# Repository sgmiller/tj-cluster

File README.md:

# tj-cluster
A custom PCB and software to drive Jeep TJ/XJ Dash clusters' CCD bus and receive CAN messages.

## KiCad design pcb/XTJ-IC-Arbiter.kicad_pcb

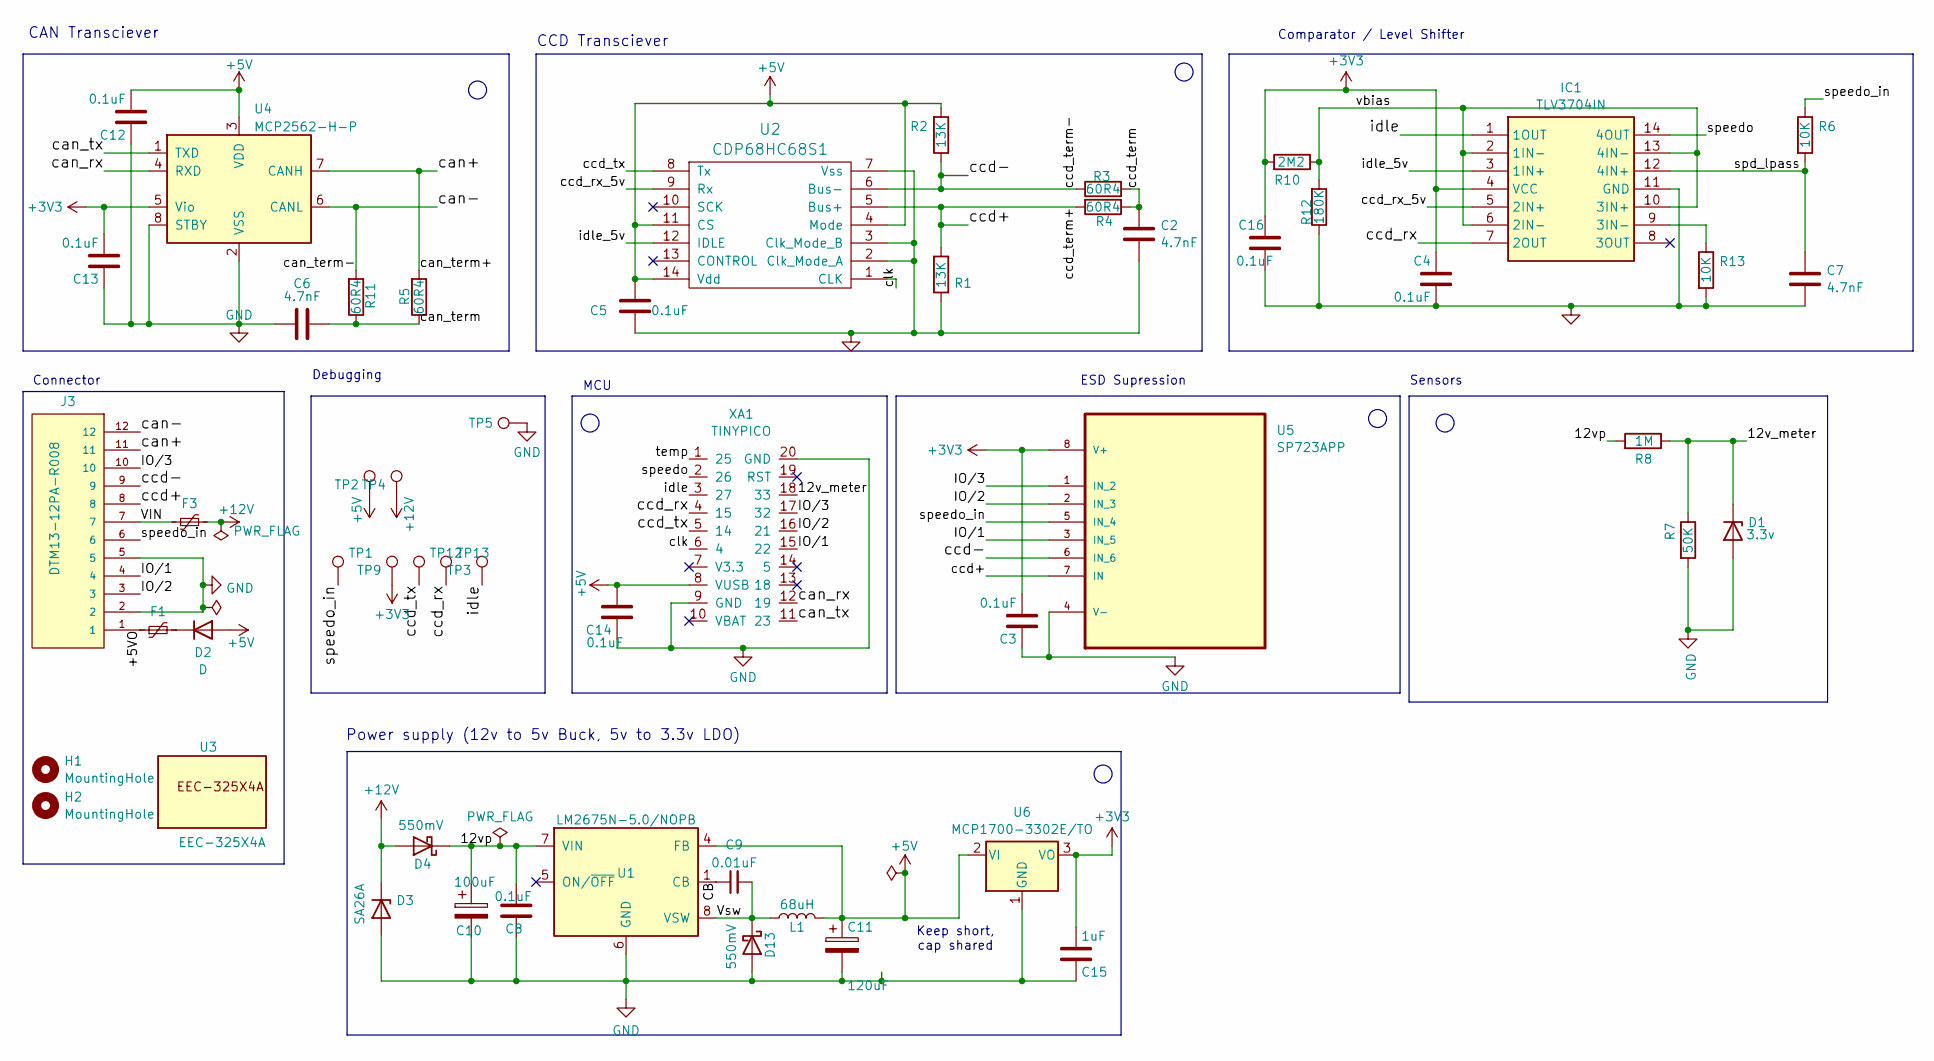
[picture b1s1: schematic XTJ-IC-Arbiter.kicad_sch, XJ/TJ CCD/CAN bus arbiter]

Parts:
C2, C6, C7: 4.7nF; C_Disc_D3.8mm_W2.6mm_P2.50mm; MPN AR151C472K4R
C3, C4, C5, C8, C12, C13, C14, C16: 0.1uF; C_Disc_D4.7mm_W2.5mm_P5.00mm; MPN K103K10X7RF53L2
C9: 0.01uF; C_Disc_D3.8mm_W2.6mm_P2.50mm; MPN K103K10X7RF53L2
C10: 100uF; C_Radial_D8.0mm_H11.5mm_P3.50mm; MPN EEU-FR1V101
C11: 120uF; CP_Radial_D8.0mm_P3.50mm; MPN EEU-FR1H121L
C15: 1uF; FA24; MPN FA24X7R1H105KRU06
D1: 3.3v; D_DO-35_SOD27_P7.62mm_Horizontal; MPN TZX3V3B-TR
D2: D; D_DO-41_SOD81_P7.62mm_Horizontal; MPN 1N40001GH
D3: SA26A; D_DO-15_P10.16mm_Horizontal; MPN SA26A; Mouser Part Number 576-SA26CA
D4, D13: 550mV; D_DO-41_SOD81_P7.62mm_Horizontal; MPN MBR160RLG
F1, F3: Polyfuse_Small; Fuse_1812_4532Metric_Pad1.30x3.40mm_HandSolder; MPN MF-MSMF050/30X-2
H1, H2: MountingHole; MountingHole_3mm
IC1: TLV3704IN; DIP794W53P254L1930H508Q14N; Mouser Part Number 595-TLV3704IN
J3: DTM13-12PA-R008; TE_DTM13-12PA-R008
L1: 68uH; L_Radial_D7.8mm_P5.00mm_Fastron_07HCP; MPN 744731680
R1, R2: 13K; R_Axial_DIN0207_L6.3mm_D2.5mm_P7.62mm_Horizontal; MPN MF1/4DC1302F
R3, R4, R5, R11: 60R4; R_Axial_DIN0207_L6.3mm_D2.5mm_P7.62mm_Horizontal; MPN CMF5560R400FHEK
R6, R13: 10K; R_Axial_DIN0207_L6.3mm_D2.5mm_P7.62mm_Horizontal; MPN MF1/4DC4701F
R7: 50K; R_Axial_DIN0207_L6.3mm_D2.5mm_P7.62mm_Horizontal; MPN MF1/4DC4701F
R8: 1M; R_Axial_DIN0207_L6.3mm_D2.5mm_P7.62mm_Horizontal; MPN MFR-25FBF52-100K
R10: 2M2; R_Axial_DIN0207_L6.3mm_D2.5mm_P7.62mm_Horizontal; MPN MF1/4LCT52R225J
R12: 180K; R_Axial_DIN0207_L6.3mm_D2.5mm_P7.62mm_Horizontal; MPN MF1/4DCT52R1803F
TP1, TP3, TP5, TP12, TP13: TestPoint; TestPoint_Loop_D2.50mm_Drill1.0mm; MPN 534-5267
TP2, TP4, TP9: TestPoint; TestPoint_Plated_Hole_D2.0mm; MPN 534-5267
U1: LM2675N-5.0/NOPB; DIP-8_W7.62mm; MPN LM2675N-5.0/NOPB
U2: CDP68HC68S1; DIP-14_W7.62mm; MPN CDP68HC68S1
U3: EEC-325X4A; TE_EEC-325X4A; PARTREV F
U4: MCP2562-H-P; DIP-8_W7.62mm; MPN MCP2562-H-P
U5: SP723APP; DIP-8_W7.62mm; MPN SP723APP
U6: MCP1700-3302E/TO; TO-92_Inline_Wide; MPN MCP1700-3302E/TO
XA1: TINYPICO

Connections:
+3V3: C3.2, C4.1, C13.2, C15.2, C16.2, IC1.4 (VCC), R10.2, TP9.1, U4.5 (Vio), U5.8 (V+), U6.3 (VO)
+5V: C5.2, C11.1, C12.2, C14.2, D2.2 (A), L1.2, R2.2, TP2.1, U1.4 (FB), U2.4 (Mode), U2.11 (CS), U2.14 (Vdd), U4.3 (VDD), U6.2 (VI), XA1.8 (VUSB)
+12V: D3.1 (K), D4.2 (A), F3.2, TP4.1
/12v_meter: D1.1 (K), R7.1, R8.1, XA1.18 (33)
/12vp: C8.2, C10.1, D4.1 (K), R8.2, U1.7 (VIN)
/+5VO: F1.1, J3.1
/CB: C9.1, U1.1 (CB)
/IO/1: J3.4, U5.3 (IN_5), XA1.15 (22)
/IO/2: J3.3, U5.2 (IN_3), XA1.16 (21)
/IO/3: J3.10, U5.1 (IN_2), XA1.17 (32)
/VIN: F3.1, J3.7
/Vsw: C9.2, D13.1 (K), L1.1, U1.8 (VSW)
/can+: J3.11, R5.2, U4.7 (CANH)
/can-: J3.12, R11.2, U4.6 (CANL)
/can_rx: U4.4 (RXD), XA1.12 (19)
/can_term: C6.2, R5.1, R11.1
/can_tx: U4.1 (TXD), XA1.11 (23)
/ccd+: J3.8, R1.2, R4.2, U2.5 (Bus+), U5.7 (IN)
/ccd-: J3.9, R2.1, R3.1, U2.6 (Bus-), U5.6 (IN_6)
/ccd_rx: IC1.7 (2OUT), TP13.1, XA1.4 (15)
/ccd_rx_5v: IC1.5 (2IN+), U2.9 (Rx)
/ccd_term: C2.2, R3.2, R4.1
/ccd_tx: TP12.1, U2.8 (Tx), XA1.5 (14)
/clk: U2.1 (CLK), XA1.6 (4)
/idle: IC1.1 (1OUT), TP3.1, XA1.3 (27)
/idle_5v: IC1.3 (1IN+), U2.12 (IDLE)
/spd_lpass: C7.2, IC1.12 (4IN+), R6.2
/speedo: IC1.14 (4OUT), XA1.2 (26)
/speedo_in: J3.6, R6.1, TP1.1, U5.5 (IN_4)
/temp: XA1.1 (25)
/vbias: IC1.2 (1IN-), IC1.6 (2IN-), IC1.10 (3IN+), IC1.13 (4IN-), R10.1, R12.2
GND: C2.1, C3.1, C4.2, C5.1, C6.1, C7.1, C8.1, C10.2, C11.2, C12.1, C13.1, C14.1, C15.1, C16.1, D1.2 (A), D3.2 (A), D13.2 (A), IC1.11 (GND), J3.2, J3.5, R1.1, R7.2, R12.1, R13.2, TP5.1, U1.6 (GND), U2.2 (Clk_Mode_A), U2.3 (Clk_Mode_B), U2.7 (Vss), U4.2 (VSS), U4.8 (STBY), U5.4 (V-), U6.1 (GND), XA1.9 (GND), XA1.20 (GND)
unnamed: D2.1 (K), F1.2
unnamed: IC1.9 (3IN-), R13.1

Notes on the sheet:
CAN Transciever
MCU
Debugging
Sensors
CCD Transciever
ESD Supression
Power supply (12v to 5v Buck, 5v to 3.3v LDO)
Keep short, cap shared
Comparator / Level Shifter
Connector

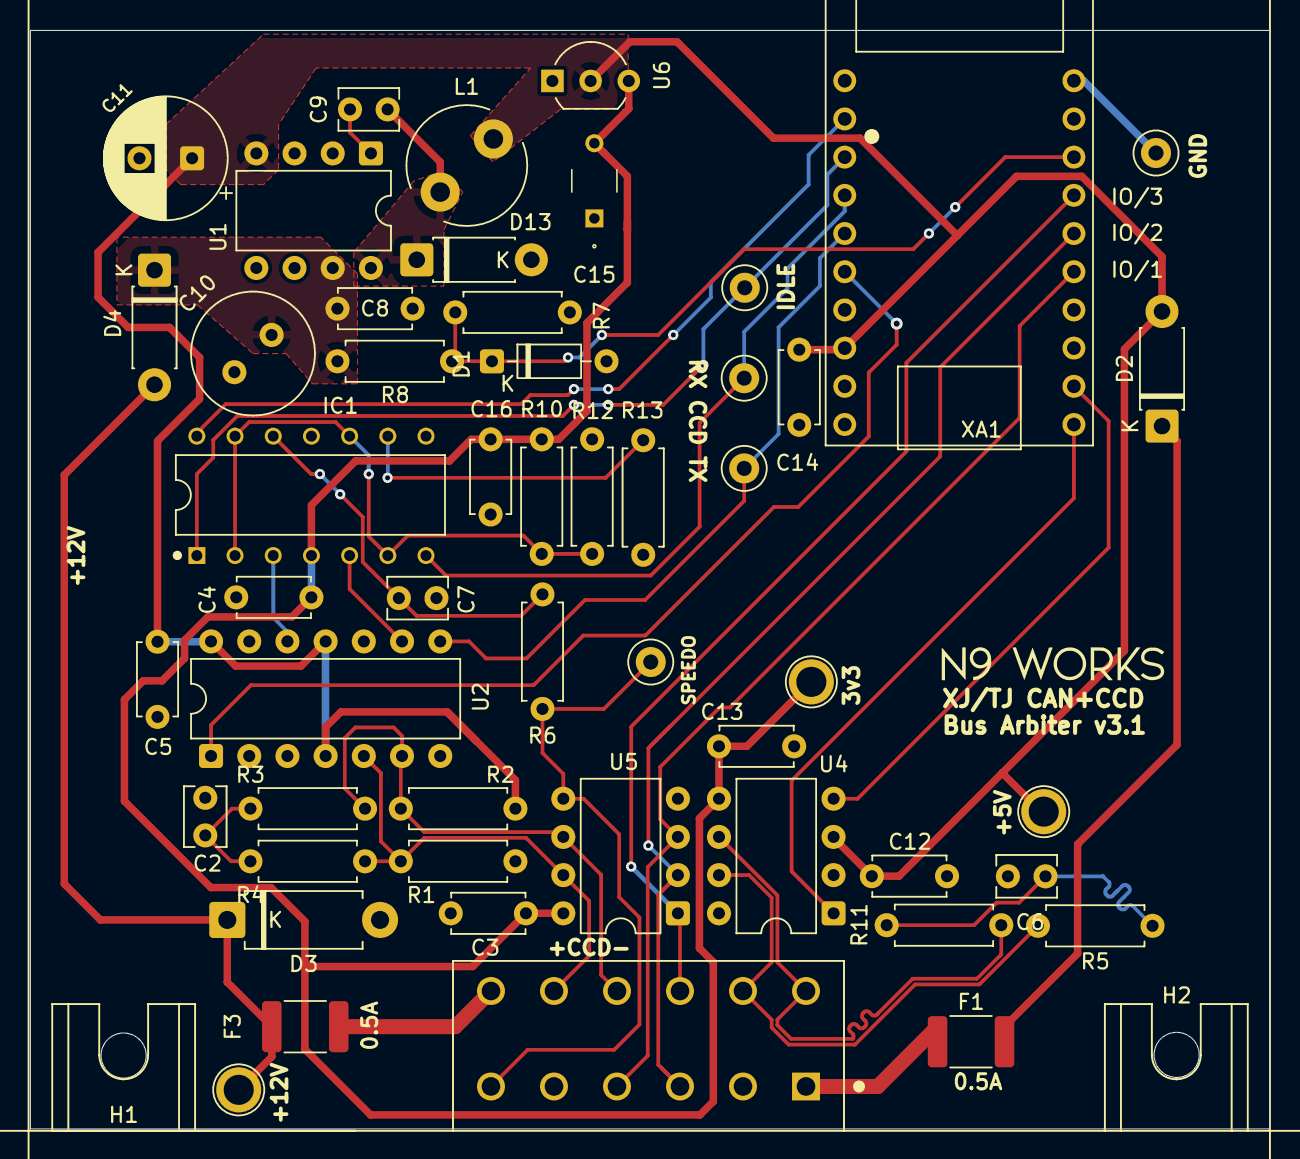
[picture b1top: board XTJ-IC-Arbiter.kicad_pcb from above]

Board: 2 copper layers, 82.4 x 73.0 mm, 54 parts (0 on the bottom side), 33 nets.

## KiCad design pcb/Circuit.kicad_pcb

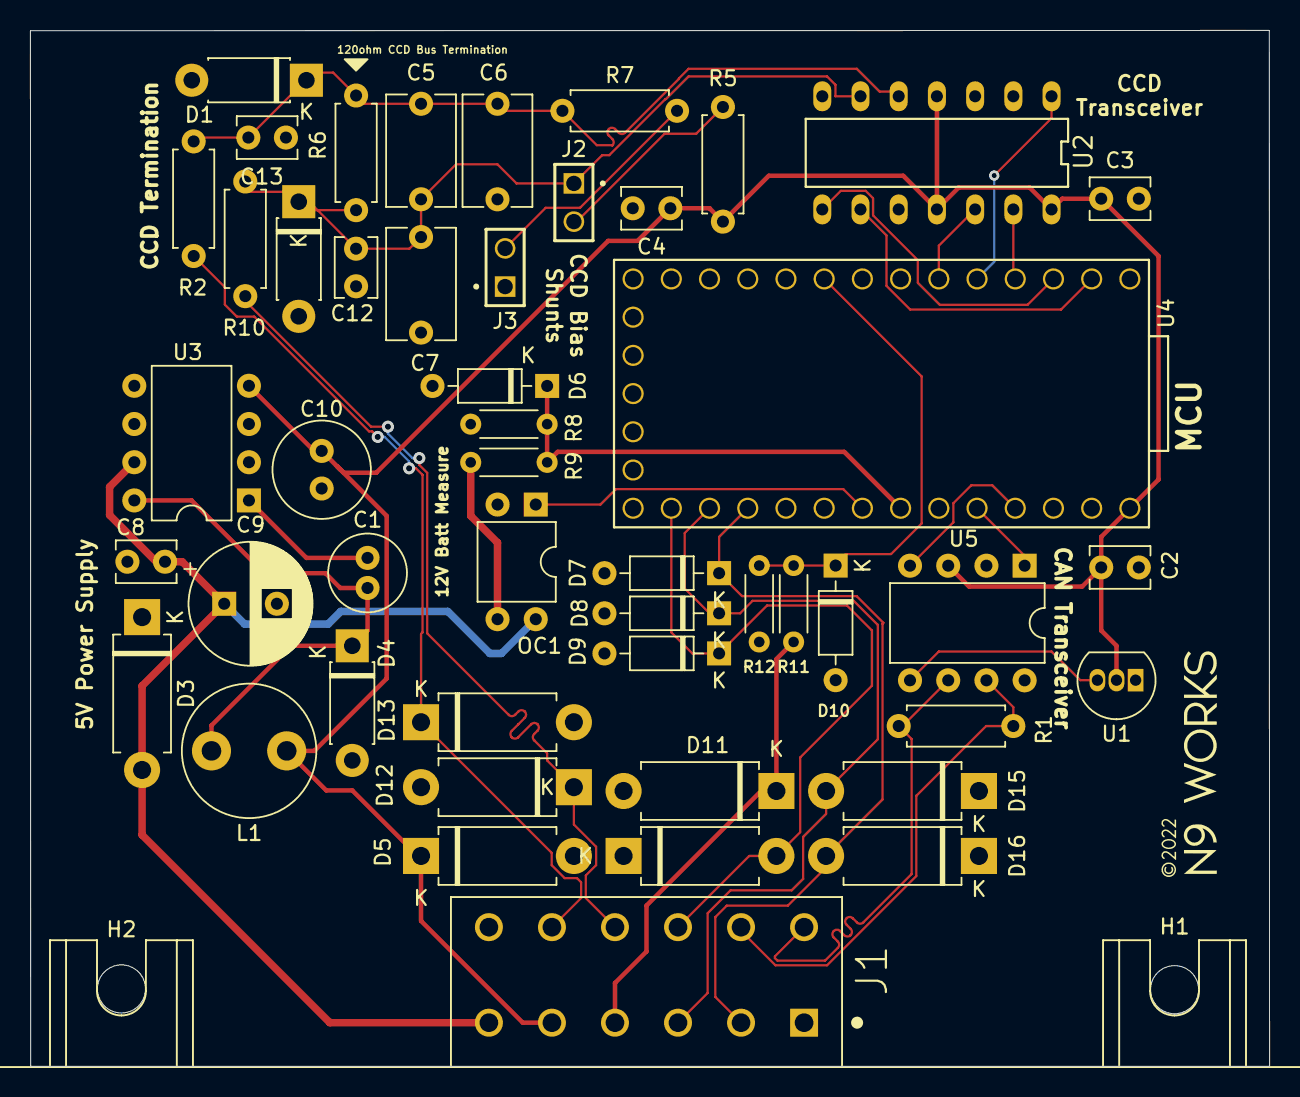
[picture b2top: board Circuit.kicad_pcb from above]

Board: 2 copper layers, 82.4 x 68.9 mm, 51 parts (0 on the bottom side), 29 nets.

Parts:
   : LOGO; N9Works
C1: 10nF; C_Radial_D5.0mm_H11.0mm_P2.00mm
C2, C3, C4: 0.1uF; C_Disc_D3.8mm_W2.6mm_P2.50mm
C5, C6, C7: 25pF; C_Disc_D6.5mm_W4mm_P6.4mm
C8: 0.1uf; C_Disc_D3.8mm_W2.6mm_P2.50mm
C9: 100uF; CP_Radial_D8.0mm_P3.50mm
C10: 68uF; C_Radial_D6.3mm_H7.0mm_P2.50mm
C12, C13: 3.3nF; C_Disc_D3.8mm_W2.6mm_P2.50mm
D1, D2: 1N4728; D_DO-41_SOD81_P7.62mm_Horizontal
D3: P6KE39CA; D_DO-15_P10.16mm_Horizontal
D4: 550mV; D_DO-41_SOD81_P7.62mm_Horizontal
D5, D14: P6KE6.8A; D_DO-15_P10.16mm_Horizontal
D6, D7, D8, D9, D10: 3.3v; D_DO-35_SOD27_P7.62mm_Horizontal
D11, D15, D16: P6KE6.8CA; D_DO-15_P10.16mm_Horizontal
D12, D13: SA5.0CA; D_DO-15_P10.16mm_Horizontal
H1, H2: MountingHole_Pad; MountingHole_3.2mm_M3
J1: DTM13-12PA-R008; TE_DTM13-12PA-R008
J2, J3: TSW-101-07-T-D; SAMTEC_TSW-101-07-T-D
L1: 47uH; L_Radial_D8.7mm_P5.00mm_Fastron_07HCP
OC1: Optocoupler_Generic; DIP-4_W7.62mm
R1, R6: 120ohm; R_Axial_DIN0207_L6.3mm_D2.5mm_P7.62mm_Horizontal
R2, R10: 10ohm; R_Axial_DIN0207_L6.3mm_D2.5mm_P7.62mm_Horizontal
R5, R7: 13K; R_Axial_DIN0207_L6.3mm_D2.5mm_P7.62mm_Horizontal
R8: 2.2Kohm; R_Axial_DIN0204_L3.6mm_D1.6mm_P5.08mm_Horizontal
R9: 13Kohm; R_Axial_DIN0204_L3.6mm_D1.6mm_P5.08mm_Horizontal
R11: 15K; R_Axial_DIN0204_L3.6mm_D1.6mm_P5.08mm_Horizontal
R12: 10K; R_Axial_DIN0204_L3.6mm_D1.6mm_P5.08mm_Horizontal
U1: MCP1700-1802E_TO92; TO-92_Inline
U2: CDP68HC68S1
U3: LM2672N-5.0; DIP-8_W7.62mm
U4: Teensy4.0; Teensy40_NoSMT
U5: MCP2562-H-P; DIP-8_W7.62mm

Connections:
12V_MEASCTL: OC1.1, U4.26 (19_A5_SCL0)
12V_MEASURE: D6.1 (K), R8.1, R9.1, U4.27 (20_A6_TX5_LRCLK1)
+5V: C2.1, C3.1, C4.1, C10.1, D5.1 (K), J1.5, L1.2, R5.1, U1.2 (VI), U2.4 (Mode), U2.11 (CS), U2.14 (Vdd), U3.4 (FB), U4.33 (VIN), U5.3 (VDD)
+12V: C8.1, C9.1, D3.2 (A), J1.6, OC1.4, U3.7 (VIN)
/1v8: U1.3 (VO), U5.5 (Vio)
CCD_CLOCK: U2.1 (CLK), U4.5 (3_LRCLK2)
GND: C2.2, C3.2, C4.2, C6.2, C7.2, C8.2, C9.2, C10.2, C12.2, C13.2, D1.2 (A), D2.2 (A), D3.1 (K), D4.2 (A), D5.2 (A), D6.2 (A), D7.2 (A), D8.2 (A), D9.2 (A), D10.2 (A), D11.1 (K), D12.2 (A), D13.2 (A), D14.2 (A), D15.1 (K), D16.1 (K), J1.1, J1.7, J3.01, OC1.2, R8.2, R12.1, U1.1 (GND), U2.2 (Clk_Mode_A), U2.3 (Clk_Mode_B), U2.7 (Vss), U3.6 (GND), U4.1 (GND), U4.17 (GND), U4.32 (GND), U5.2 (VSS), U5.8 (STBY)
IO/1: D7.1 (K), D16.2 (A), J1.2, U4.23 (16_A2_RX4_SCL1)
IO/2: D8.1 (K), D15.2 (A), J1.3, U4.22 (15_A1_RX3_SPDIF_IN)
IO/3: D9.1 (K), D11.2 (A), J1.10, U4.21 (14_A0_TX3_SPDIF_OUT)
unnamed: C1.1, U3.1 (CB)
unnamed: C1.2, D4.1 (K), L1.1, U3.8 (VSW)
unnamed: J2.02, R5.2
unnamed: J3.02, R7.2
unnamed: OC1.3, R9.2
SPEEDO: D10.1 (K), R11.1, R12.2, U4.9 (7_RX2_OUT1A)
SPEEDO_IN: D14.1 (K), J1.4, R11.2
can+: J1.11, R1.1, U5.7 (CANH)
can-: J1.12, R1.2, U5.6 (CANL)
can_rx: U4.30 (23_A9_CRX1_MCLK1), U5.4 (RXD)
can_tx: U4.29 (22_A8_CTX1), U5.1 (TXD)
ccd+: D13.1 (K), J1.8, R2.1
ccd-: D12.1 (K), J1.9, R10.1
ccd_f+: C5.1, C6.1, C13.1, D1.1 (K), R2.2, R6.1, R7.1, U2.5 (Bus+)
ccd_f-: C5.2, C7.1, C12.1, D2.1 (K), J2.01, R6.2, R10.2, U2.6 (Bus-)
ctrl: U2.13 (CONTROL), U4.4 (2_OUT2)
idle: U2.12 (IDLE), U4.6 (4_BCLK2)
rxd: U2.9 (Rx), U4.2 (0_RX1_CRX2_CS1)
txd: U2.8 (Tx), U4.3 (1_TX1_CTX2_MISO1)

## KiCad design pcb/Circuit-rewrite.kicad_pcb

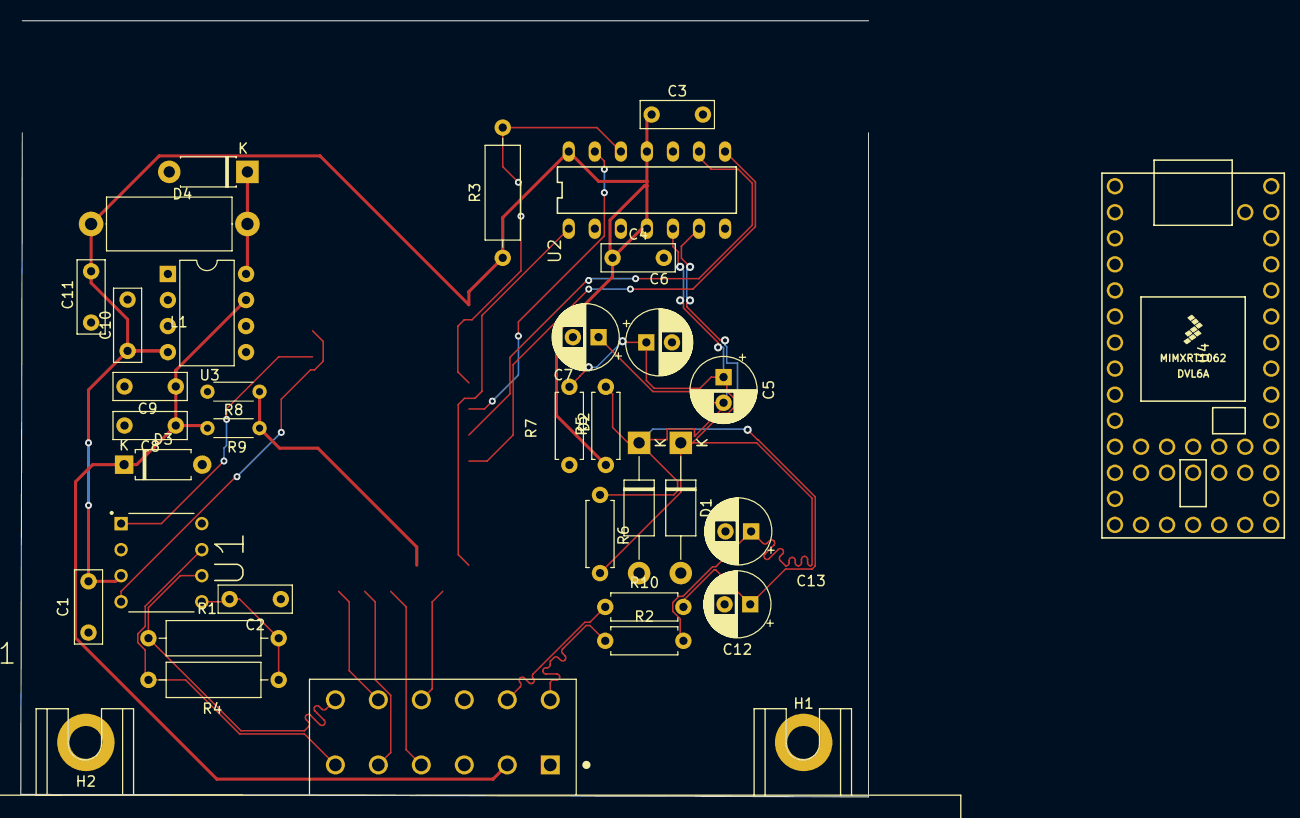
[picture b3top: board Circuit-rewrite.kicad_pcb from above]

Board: 2 copper layers, 82.7 x 75.7 mm, 35 parts (0 on the bottom side), 23 nets.

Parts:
C1, C3, C4: 0.1uF; C_Disc_D7.0mm_W2.5mm_P5.00mm
C2: 4700pF; C_Disc_D7.0mm_W2.5mm_P5.00mm
C5, C6, C7: 25pF; CP_Radial_D6.3mm_P2.50mm
C8, C11: 0.1uf; C_Disc_D7.0mm_W2.5mm_P5.00mm
C9: 100uf; C_Disc_D7.0mm_W2.5mm_P5.00mm
C10: 150uF; C_Disc_D7.0mm_W2.5mm_P5.00mm
C12, C13: 3.3nF; CP_Radial_D6.3mm_P2.50mm
D1, D2: 1N4728; D_DO-41_SOD81_P12.70mm_Horizontal
D3: SD15_SOD323; D_A-405_P7.62mm_Horizontal
D4: 550mV; D_DO-41_SOD81_P7.62mm_Horizontal
H1, H2: MountingHole_Pad; MountingHole_3.2mm_M3_DIN965_Pad
J1: DTM13-12PA-R008; TE_DTM13-12PA-R008
L1: 150uH; L_Axial_L12.0mm_D5.0mm_P15.24mm_Horizontal_Fastron_MISC
R1, R4: 60ohm; R_Axial_DIN0309_L9.0mm_D3.2mm_P12.70mm_Horizontal
R2, R10: 10ohm; R_Axial_DIN0207_L6.3mm_D2.5mm_P7.62mm_Horizontal
R3: 10k; R_Axial_DIN0309_L9.0mm_D3.2mm_P12.70mm_Horizontal
R5, R7: 13K; R_Axial_DIN0207_L6.3mm_D2.5mm_P7.62mm_Horizontal
R6: 120ohm; R_Axial_DIN0207_L6.3mm_D2.5mm_P7.62mm_Horizontal
R8: 1.5M; R_Axial_DIN0204_L3.6mm_D1.6mm_P5.08mm_Horizontal
R9: 10M; R_Axial_DIN0204_L3.6mm_D1.6mm_P5.08mm_Horizontal
U1: MCP2561; DIP787W46P254L927H533Q8
U2: CDP68HC68S1
U3: LM2594HVM-5.0; DIP-8_W7.62mm
U4: Teensy4.0; Teensy40

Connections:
12V_MEASURE: R8.1, R9.1, U4.38 (27_A13_SCK1)
+5V: C1.2, C3.1, C4.1, C10.1, C11.1, L1.2, R3.1, R5.1, U1.3 (VDD), U2.4 (Mode), U2.11 (CS), U2.14 (Vdd), U3.4 (FB), U4.33 (VIN)
+12V: C8.1, C9.1, D3.1 (A1), J1.2, R9.2, U3.7 (VIN)
/IO/1: J1.8, U4.43 (32_OUT1B)
/IO/2: J1.9, U4.35 (24_A10_TX6_SCL2)
/IO/3: J1.5, U4.41 (30_CRX3)
/IO/4: J1.4, U4.39 (28_RX7)
CCD_CLOCK: U2.1 (CLK), U4.23 (16_A2_RX4_SCL1)
GND: C1.1, C2.1, C3.2, C4.2, C6.2, C7.2, C8.2, C9.2, C10.2, C11.2, C12.2, C13.2, D1.2 (A), D2.2 (A), D3.2 (A2), D4.2 (A), H1.1, H2.1, J1.1, R7.2, R8.2, U1.2 (VSS), U2.2 (Clk_Mode_A), U2.3 (Clk_Mode_B), U2.7 (Vss), U3.1 (NC), U3.2 (NC), U3.3 (NC), U3.5 (~ON/OFF), U3.6 (GND), U4.1 (GND), U4.17 (GND), U4.32 (GND)
unnamed: C2.2, R1.2, R4.1, U1.5 (SPLIT)
unnamed: D4.1 (K), L1.1, U3.8 (OUT)
can+: J1.6, R1.1, U1.7 (CANH)
can-: J1.7, R4.2, U1.6 (CANL)
can_rx: U1.4 (RXD), U4.2 (0_RX1_CRX2_CS1)
can_tx: U1.1 (TXD), U4.3 (1_TX1_CTX2_MISO1)
ccd+: J1.12, R2.1
ccd-: J1.11, R10.1
ccd_f+: C5.1, C6.1, C13.1, D1.1 (K), R2.2, R6.1, R7.1, U2.5 (Bus+)
ccd_f-: C5.2, C7.1, C12.1, D2.1 (K), R5.2, R6.2, R10.2, U2.6 (Bus-)
ctrl: U2.13 (CONTROL), U4.29 (22_A8_CTX1)
idle: R3.2, U2.12 (IDLE), U4.30 (23_A9_CRX1_MCLK1)
rxd: U2.9 (Rx), U4.28 (21_A7_RX5_BCLK1)
txd: U2.8 (Tx), U4.27 (20_A6_TX5_LRCLK1)

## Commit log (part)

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2022-02-06 Initial PlatformIO setup
2022-05-31 Initial success
2022-06-02 begin abstraction
2022-06-03 Working speedometer
2022-06-05 Add PCB
2022-06-05 Add gitignore
2022-06-08 Working oil and battery gauges
2022-06-08 Not these
2022-06-08 Cleanup code, add all instruments
2022-06-08 speedometer
2022-06-08 make constant
2022-06-09 Implement Teensy watchdog, and light the SKIM lamp if we reset due to it
2022-06-09 Code for speedometer handling and odometer increment (not quite)
2022-06-09 More git ignore
2022-06-10 Blink onboard LED on activity
2022-06-10 Airbag handling
2022-06-10 more tweaks
2022-06-11 commit before changing can transceiver
2022-06-12 Save design with LEDs
2022-06-14 Move IO pins to more useful Teensy pins
2022-06-14 Add footprints
2022-06-14 linting
2022-06-14 remove gerbers
2022-06-14 more footprints
2022-06-14 Update teensy footprint
2022-06-14 Remove unnecessary files
2022-06-15 Start self test mode
2022-06-15 Found upshift and cruise, added to selftest
2022-06-15 get rid of ancient rewrite
2022-06-16 Move speedo to a FlexPWM pin
2022-06-24 Update for actual parts ordered from Mouser
2022-06-27 Circuit using LM2591HVT
2022-06-28 CDP 3d model
2022-06-28 Tidy up capacitors
2022-06-28 move via cleanup
2022-06-29 Add overvoltage protection to the 12v measure pin
2022-06-29 Implement odometer increment
2022-06-30 Add 3.3v overvolt protection zeners
2022-06-30 Use correctly sized TVS diodes for the CCD bus
2022-06-30 Move CCD lines farther from power
2022-06-30 Silkscreen tweaks
2022-07-01 Undo attempt to simplify jumpers
2022-07-01 Project rename
2022-07-01 Complete rename
2022-07-01 Refactor away the need for interval timers, which we have in limited quantity
2022-07-05 Multi-CCD experiment
2022-07-05 fix activity
2022-07-05 Add voltage divider for idle
2022-07-05 rearrange
2022-07-08 series resistor for idle in
2022-07-08 ignore fab
2022-07-08 More small tweaks
2022-07-08 Copy changes from the multi-ccd branch
2022-07-08 Rationalize CCD filters
2022-07-09 Re-add TVS diodes to CCD inputs
2022-07-09 Geographical reannotate
2022-07-09 Experiment with a TVS IC
2022-07-10 Slightly reorganize TVS matrix to clean up traces
2022-07-10 gitignore
2022-07-17 remove mounting grounds
2022-07-17 Shorten distance to bypass capacitor
2022-07-17 After breadboarding, eliminate LDO reference regulator
2022-07-17 Correct DRC errors
2022-07-17 Add parallel traces to CAN/CCD routes so there is still a connection if the 120ohm resistor is cut
2022-07-18 More tweaking
2022-07-18 Switch from jumpers to DIP switches for CCD bias, CCD bus termination. Add DIP switch for selectable CAN bus termination. DIP switches should hold up in vibration, where I worry a jumper might rattle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
2022-07-18 Some hypothetical CAN handling for the AEM VCU
2022-07-19 Add a level shifter to handle 5v to 3.3v for the CDP<->Teensy
2022-07-19 tidy wiring
2022-07-21 Tidy up even more vias
2022-07-21 Improve a couple grounds
2022-07-24 Concept ignoring all CCD RX
2022-07-24 cleanup
2022-07-24 diff tuning
2022-07-26 Switch to a MOSFET array
2022-07-27 Switch to simpler THT transistors
2022-07-27 Rewire
2022-07-27 tweak
2022-07-27 Try to change to 3.3v
2022-07-27 Design using the CDP transceiver but in TX only, neglecting idle etc
2022-07-27 Add repeated refresh of all instruments
2022-07-28 Rearrange for tighter CCD signal traces
2022-07-28 CCD length tuning
2022-07-28 Fully working self test!
2022-07-28 Tweak CCD routing just a bit more
2022-07-29 Measure battery more frequently
2022-07-29 Straightforward airbag interval handling
2022-07-29 Eureka! Finally satisfied with CCD traces
2022-07-29 One more bypass cap
2022-07-30 Last minute tweaks and board shrink
2022-07-31 Footprint double-checks
2022-07-31 Correct and arrange power components
2022-07-31 Don't crowd the ground
2022-07-31 Fix battery calculation
2022-07-31 Fix auto-refresh logic
2022-07-31 CCD length tune
2022-07-31 Last tweaks before manufacture
2022-07-31 Correct one of the ESD diodes
2022-08-01 Add a readme for the source code
2022-08-01 formatting
2022-08-01 speedo note
2022-09-10 Fixes for CCD filter network
2022-09-10 and schematic
2022-09-10 Re-length tune
2022-09-10 Accidental commit
2022-09-11 Add a couple backup traces
2022-09-12 Correct orientation of CCD chip, which was electrically sound but the 3D model was backwards
2022-09-17 More mods for 1.1
2022-10-16 Don't place 5v and 12v pins side by side
2022-10-16 Add overvoltage protection on the 5v line
2022-10-16 move k
2022-10-18 Add a test header
2024-05-24 Fixes prior to simplification
2024-05-24 not a success
2024-05-25 Get rid of errors
2024-05-25 Finished!
2024-05-25 exclusions
2024-05-26 tune can termination length
2024-05-26 fix board edge
2024-05-26 cleanup bypass caps
2024-05-26 get rid of 5v feed text
2024-05-26 convert unused pin to gnd
2024-05-26 fix 3d model offset for connectr
2024-05-26 3.3v conn
2024-05-26 safer 3.3v trace
2024-05-26 drc fixes
2024-05-26 fix orphaned c9
2024-05-26 fix unconnected pullup
2024-05-26 one more bypass
2024-05-26 resolve
2024-05-26 Switch to single pole dip switches for CCD/CAN termination
2024-05-27 warnings
2024-05-27 elminate some vias
2024-05-27 current limiting on the ssd, tune can length
2024-05-27 Fix TVS diode for 12v to have reasonable working/breakdown ranges
2024-05-28 current limit the 12v measure prior to the ssd
2024-05-28 cleanup schematic
2024-05-28 get input capacitor closer to power ic
2024-05-28 Tune CAN lengths
2024-05-28 labels
2024-05-28 logo & copyright
2024-05-28 bypass cap for tvs array
2024-05-29 tune ccd bus length
2024-05-30 death to vias
2024-06-01 Recalculate the 12v measure voltage dividers, and add a zener to limit to 3.3v
2024-06-01 ugly but functional
2024-06-01 less ugly
2024-06-01 polish, text
2024-06-01 oshpark colors
2024-06-04 no battery relay
2024-06-06 bigger courtyard for the ccd module
2025-08-30 Update to KiCad 9
2025-08-31 Fix labels
2025-09-02 Working v3 layout
2025-09-02 other parts
2025-09-02 Silkscreen cleanup
2025-09-02 more updates
2025-09-02 update pins
2025-09-02 differential skew tuning
2025-09-04 drive towards 0 errors
2025-09-04 ignore KiCad locks
2025-09-04 Software pin updates, label test points on PCB
2025-09-04 Correct the power supply Cout specs
2025-09-06 Power 3.3v via a separate LDO rather than from the Teensy
2025-09-07 Add tons of detail and fixes to particular part numbers and footprints
2025-09-07 part data
2025-09-08 Swich to jumpers for bus termination
2025-09-08 Cleanup labels
2025-09-08 Fix buffer footprint
2025-09-08 Teensy 3D model
2025-09-08 change tx/rx pins
2025-09-08 ERC fixes
2025-09-09 Ditch test points for vertical passives
2025-09-09 More layout tweaks, mostly around power
2025-09-10 Version using a TinyPICO ESP32 board
2025-09-10 fix CAN SPLIT termination
2025-09-12 Get BOM part #s correct
2025-09-12 further work on specifying components
2025-09-13 schematic cleanup
2025-09-13 Switch from label to proper power symbol for 3.3v
2025-09-15 Add a transistor to boost a weak speedo signal
2025-09-16 Add input cap for LDO
2025-09-17 update for parts I can actually purchase
2025-09-17 Avoid routing under the antenna
2025-09-17 even more
2025-09-17 remove probably bad idea diode
2025-09-18 Continued routing improvements
2025-09-18 vscode settings
2025-09-20 Add the correct TE footprint including courtyard. Update antenna keep-out, more finesse
2025-09-20 Fix gnd plane
2025-09-20 Fix last minute inconsistencies
2025-09-20 among other things, creating more USB connector clearance
2025-09-20 length tune the extended I/Os, making it at least possible to use them for high speed signals
2025-09-20 Keep voltage test points at board edge to avoid shorts
2025-09-20 fix DRC errors
2025-09-20 silkscreen fixes
2025-09-23 Re-layout power supply based on TI guidance and getting to know copper pours
2025-09-23 tidy up schematic
2025-09-23 add enclosure symbol/footprint
2025-09-23 still working to keep a clean ground plane
2025-09-24 try and fix the position of the enclosure keepout
2025-09-24 Lock board, enclosure, edge cuts, and connector
2025-09-24 F.Cu ground pour
2025-09-26 Continued pour zone optimization
2025-09-27 Keep power traces 0.05in from board edge, via rule
2025-09-27 Via stitching
2025-09-27 tie unused GPIOs to GND
2025-09-27 dont actually connect pins to ground, as that could result in a short if the pin is configured as output
2025-09-27 Get 12v measure closer to source
2025-09-29 uniform power net, shielding via stitching
2025-09-29 ensure ext I/Os are length tuned
2025-10-01 Speedo needs an internal pullup
2025-10-01 After the 4 layer adventure, cleanup
2025-10-03 Hand tune the differential lengths (CAD/CCD)
2025-10-03 silkscreen work
2025-10-04 re-route some traces to get contiguous front ground pours without vias
2025-10-06 LDO caps were the wrong footprint
2025-10-07 Other footprint fixes
2025-10-07 colorize crucial nets
2025-10-07 fusing
2025-10-08 12v inrush limiting
2025-10-08 use a slow blow fuse to avoid a heat producing inrush resistor
2025-10-11 Add comparator
2025-10-12 Layout tweaks
2025-10-12 resolve erc/drc errors
2025-10-12 net clarification
2025-10-13 tidy
2025-10-15 Add an ambient thermometer, and use it to sleep the ESP32 if we get too hot. Presumably it'll be the MCU that gets us there
2025-10-15 move it to a cleaner spot
2025-10-15 aesthetics
2025-10-17 relayout the board to get the antenna out to the edge with no copper beneath
2025-10-18 work on eliminating b.cu routes
2025-10-18 Fix CDP clock signal
2025-10-18 Lots of the signals coming out of the CDP are >0v at low, provide a ref volt for V- to the comparator for those
2025-10-18 respond to erc violations
2025-10-18 USB connector keepout
2025-10-18 stiching vias
2025-10-19 make the comparator's VREF configurable in the MCU
2025-10-19 Turns out the ESP32 DAC isn't very clean on analog, so use a voltage divider/RC for the comparator reference
2025-10-20 fix rule violations
2025-10-20 Double check and tune board edges
2025-10-22 Wrong TVS diode for 12v, need only be uni-dir
2025-10-22 dev env files
2025-10-23 reduce ground via tracks
2025-10-23 missed swapping the tvs diode bypass cap when rotating
2025-10-28 Some more routing opt, fix up ref labels
2025-10-30 Wider base track widths, stitching vias
2025-10-31 improve clearance
2025-10-31 eliminate f.cu pour
2025-10-31 dont overthink tinypico thermals
2025-10-31 via elimination
2025-10-31 re-tune CCD traces
2025-11-01 more iteration
2025-11-02 better isolation of power traces and power pins in the connector
2025-11-06 Working Bluetooth serial
2025-11-06 .gitignore
2025-11-07 Switch to 1a fast blow fuses.
2025-11-07 use conditional code for self-test vs normal etc
2025-11-08 re-layout switcher for lower emi
2025-11-08 Lots of fun cleanup made possible by the supply re-layout
2025-11-08 silkscreen
2025-11-10 battery wip
2025-11-10 change bat vdiv values
2025-11-12 Add an input side diode to the regulator circuit to prevent reverse voltage when USB is connected but 12v is not
2025-11-12 schottky on output too
2025-11-14 work on math for speedo
2025-11-15 teardrop power nets
2025-11-15 fix comparator unused input
2025-11-15 unify the 4.7nF caps
2025-11-15 Global to local labels
2025-11-15 schematic tidying
2025-11-16 attempt to keep traces clear of pads, remove unnecessary opts
2025-11-16 unsaved changes
2025-11-16 thermo code
2025-11-16 Serial->stdout
2025-11-17 Flip CAN chip to get more clearance for the USB connector
2025-11-18 Finished CAN validation
2025-11-18 Switch to resettable fuses and delete the 5v out diode (too much forward voltage drop)
2025-11-19 Switch to SMT resettable fuses
2025-11-19 Second schematic/project for bench validating CAN via a second Teensy MCU
2025-11-19 power notes
2025-11-19 gitignore update
2025-11-19 mv headers
2025-11-19 route speed/idle through via to avoid sig over gap
2025-11-19 one more tweak
2025-11-19 last minute change
2025-12-12 work on efficient xmit
2025-12-17 Starting v3.1: USB cable is too tight a fit on v3.0, make more room even for a right angle connector
2025-12-17 use some signal vias to simplify power distribution
2025-12-18 cleanup 90s
2025-12-27 fix some erc probs
2026-05-04 dont fear the via
2026-05-05 larger power traces

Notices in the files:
pcb/Circuit-rewrite.kicad_pcb:
TJ Cluster v1.0 © 2022
Licensed under CC BY-NC-SA 4.0
pcb/Circuit.kicad_pcb:
© 2022 Scott Miller/N9 Works
